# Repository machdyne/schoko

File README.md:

# Schoko Computer

Schoko is an FPGA computer designed by Lone Dynamics Corporation.

This repo contains schematics, pinouts, a 3D-printable case, example gateware and documentation.

Find more information on the [Schoko product page](https://machdyne.com/product/schoko-computer/).

## Programming Schoko

Schoko has a JTAG interface and ships with a [DFU bootloader](https://github.com/machdyne/tinydfu-bootloader) that allows the included flash [MMOD](https://machdyne.com/product/mmod) to be programmed over the USB-C port.

The first 1MB of the flash MMOD is reserved for the bootloader, the next 3MB are reserved for user gateware and the remaining space is available for user data.

### DFU

The DFU bootloader is available for 5 seconds after power-on, issuing a DFU command during this period will stop the boot process until the DFU device is detached. If no command is received the boot process will continue and the user gateware will be loaded.

Install [dfu-util](http://dfu-util.sourceforge.net) (Debian/Ubuntu):

```
$ sudo apt install dfu-util
```

Update the user gateware on the flash MMOD:

```
$ sudo dfu-util -a 0 -D image.bit
```

Detach the DFU device and continue the boot process:

```
$ sudo dfu-util -a 0 -e
```

It is possible to update the bootloader itself using DFU but you shouldn't attempt this unless you have a JTAG programmer (or another method to program the MMOD) available, in case you need to restore the bootloader.

### JTAG

These examples assume you're using a "USB Blaster" JTAG cable, see the header pinout below. You will need to have [openFPGALoader](https://github.com/trabucayre/openFPGALoader) installed.

Program the configuration SRAM:

```
openFPGALoader -c usb-blaster image.bit
```

Program the flash MMOD:

```
openFPGALoader -f -c usb-blaster images/bootloader/tinydfu_schoko.bit
```

## Blinky 

Building the blinky example requires [Yosys](https://github.com/YosysHQ/yosys), [nextpnr-ecp5](https://github.com/YosysHQ/nextpnr) and [Project Trellis](https://github.com/YosysHQ/prjtrellis).

Assuming they are installed, you can simply type `make` to build the gateware, which will be written to output/blinky.bin. You can then use [openFPGALoader](https://github.com/trabucayre/openFPGALoader) or dfu-util to write the gateware to the device.

## Linux

See the [Kakao Linux](https://github.com/machdyne/kakao) repo for the latest instructions.

### Prebuilt Images

Copy the files from the `images/linux` directory to the root directory of a FAT-formatted MicroSD card.

Schoko ships with LiteX gateware on the user gateware section of the MMOD that is compatible with these images. If you plug a USB-UART into PMODA you should be able to interact with LiteX and view the Linux boot messages. After several seconds the Linux penguin should appear on the screen (HDMI) followed by a login prompt.

You can switch to the VGA gateware with:
 
```
$ sudo dfu-util -a 0 -D images/v1_vga/schoko.bit
```

Note: It should be possible to store the Linux images on the MMOD itself and boot Linux without any MicroSD card but this is not yet supported.

### Building Linux

Please follow the setup instructions in the [linux-on-litex-vexriscv](https://github.com/litex-hub/linux-on-litex-vexriscv) repo and then:

1. Build the Linux-capable gateware:

```
$ cd linux-on-litex-vexriscv
$ ./make.py --board schoko --uart-baudrate 1000000 --build
$ ls build/schoko
```

2. Write the gateware to the MMOD using USB DFU:

```
$ sudo dfu-util -a 0 -D build/schoko/gateware/schoko.bit
```

3. Copy the device tree binary `build/schoko/schoko.dtb` to a FAT-formatted MicroSD card.

4. Build the Linux kernel and root filesystem:

```
$ cd ..
$ git clone http://github.com/buildroot/buildroot
$ cd buildroot
$ make BR2_EXTERNAL=../linux-on-litex-vexriscv/buildroot/ litex_vexriscv_usbhost_defconfig
```

Optionally customize the kernel and buildroot packages:

```
$ make menuconfig
```

Build the kernel and rootfs:

```
$ make
$ ls output/images
```

5. Copy the `Image` and `rootfs.cpio` files from output/images to the MicroSD card.

6. Copy the OpenSBI binary (included in this repo as `schoko/images/linux/opensbi.bin`) to the MicroSD card. Alternatively, you can build this binary by following [these instructions](https://github.com/litex-hub/linux-on-litex-vexriscv#-generating-the-opensbi-binary-optional).

7. Copy `schoko/images/linux/boot.json` to the MicroSD card.

8. Power-cycle Schoko and if a USB-UART PMOD is attached to PMODA you should see the LiteX memory test and then the Linux boot messages. After Linux has finished booting you should see a login prompt on the serial console and the HDMI display.

## LiteX

### Installing LiteX

If you haven't yet installed LiteX please see the [LiteX quick start guide](https://github.com/enjoy-digital/litex#quick-start-guide) for details on installing LiteX.

### Building Custom Gateware

Build the LiteX gateware:

```
$ cd litex-boards/litex_boards/targets
$ ./machdyne_schoko.py --cpu-type=vexriscv --cpu-variant=lite --sys-clk-freq 40000000 --uart-baudrate 1000000 --uart-name serial --build
```

Program the LiteX gateware to SRAM over JTAG:

```
$ ./machdyne_schoko.py --cable usb-blaster --load
```

Or program the LiteX gateware to flash over DFU:

```
$ sudo dfu-util -a 0 -D build/machdyne_schoko/gateware/machdyne_schoko.bit
```

## JTAG Header

The JTAG header can be used to program the FPGA SRAM as well as the MMOD flash memory. 

```
1 2
3 4
5 6
```

| Pin | Signal |
| --- | ------ |
| 1 | TCK |
| 2 | TDI |
| 3 | TDO |
| 4 | TMS |
| 5 | 3V3 |
| 6 | GND |

## Board Revisions

| Revision | Notes |
| -------- | ----- |
| V0 | Internal prototype |
| V1 | Initial production boards |
| V1A | Identical to V1 except for minor aesthetic changes on the silkscreen |
| V2 | Work-in-progress; adds SD-mode for MicroSD card |

## License

The contents of this repo are released under the [Lone Dynamics Open License](LICENSE.md) with the following exceptions:

- The KiCad design files contain parts of the [kicad-pmod](https://github.com/mithro/kicad-pmod) library which is released under the [Apache License, Version 2.0](https://www.apache.org/licenses/LICENSE-2.0.html).

- The KiCad design files may contain symbols and footprints released under other licenses; please contact us if we've failed to give proper attribution.

Note: You can use these designs for commercial purposes but we ask that instead of producing exact clones, that you either replace our trademarks and logos with your own or add your own next to ours.

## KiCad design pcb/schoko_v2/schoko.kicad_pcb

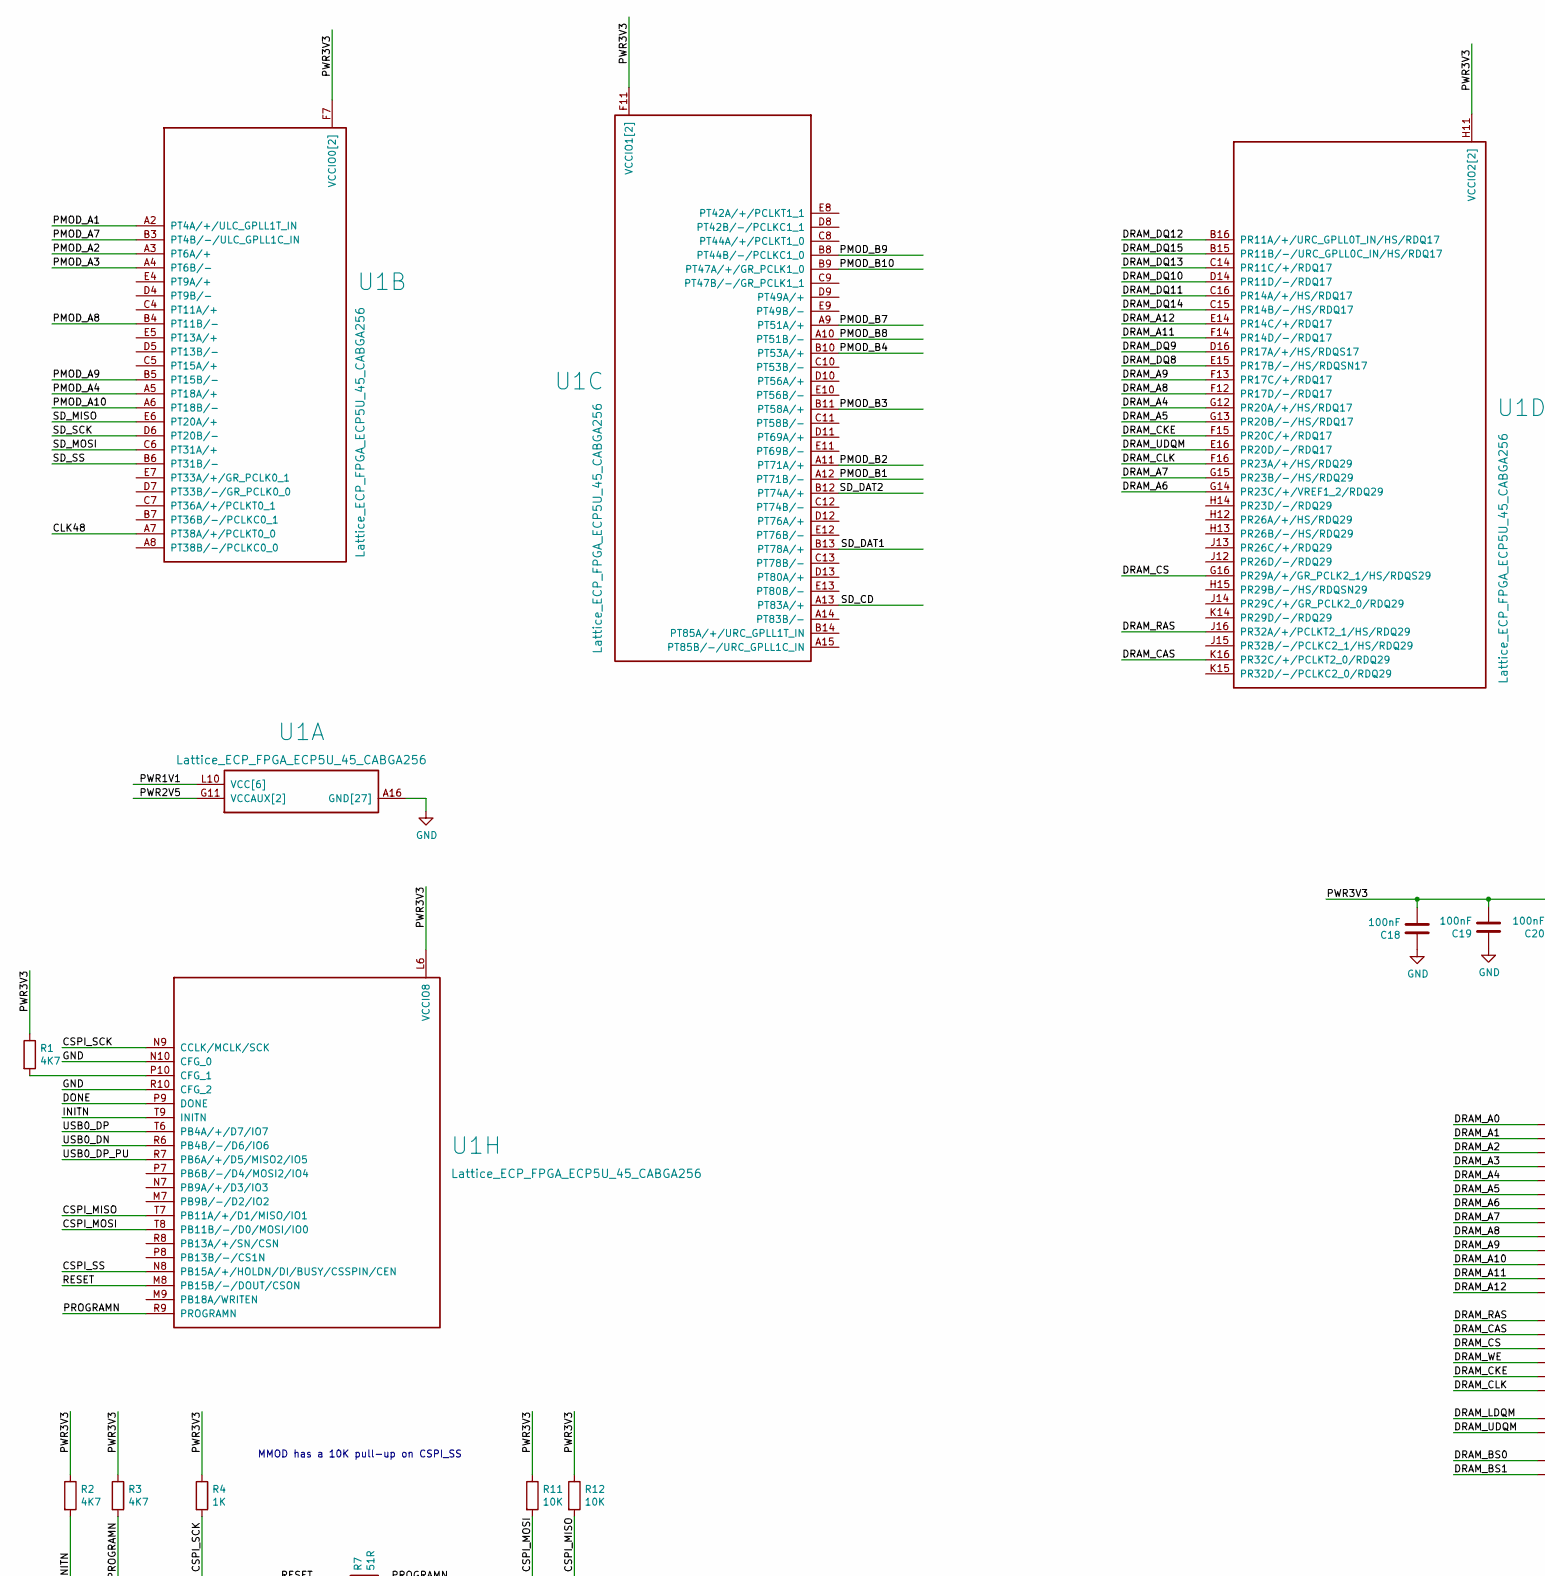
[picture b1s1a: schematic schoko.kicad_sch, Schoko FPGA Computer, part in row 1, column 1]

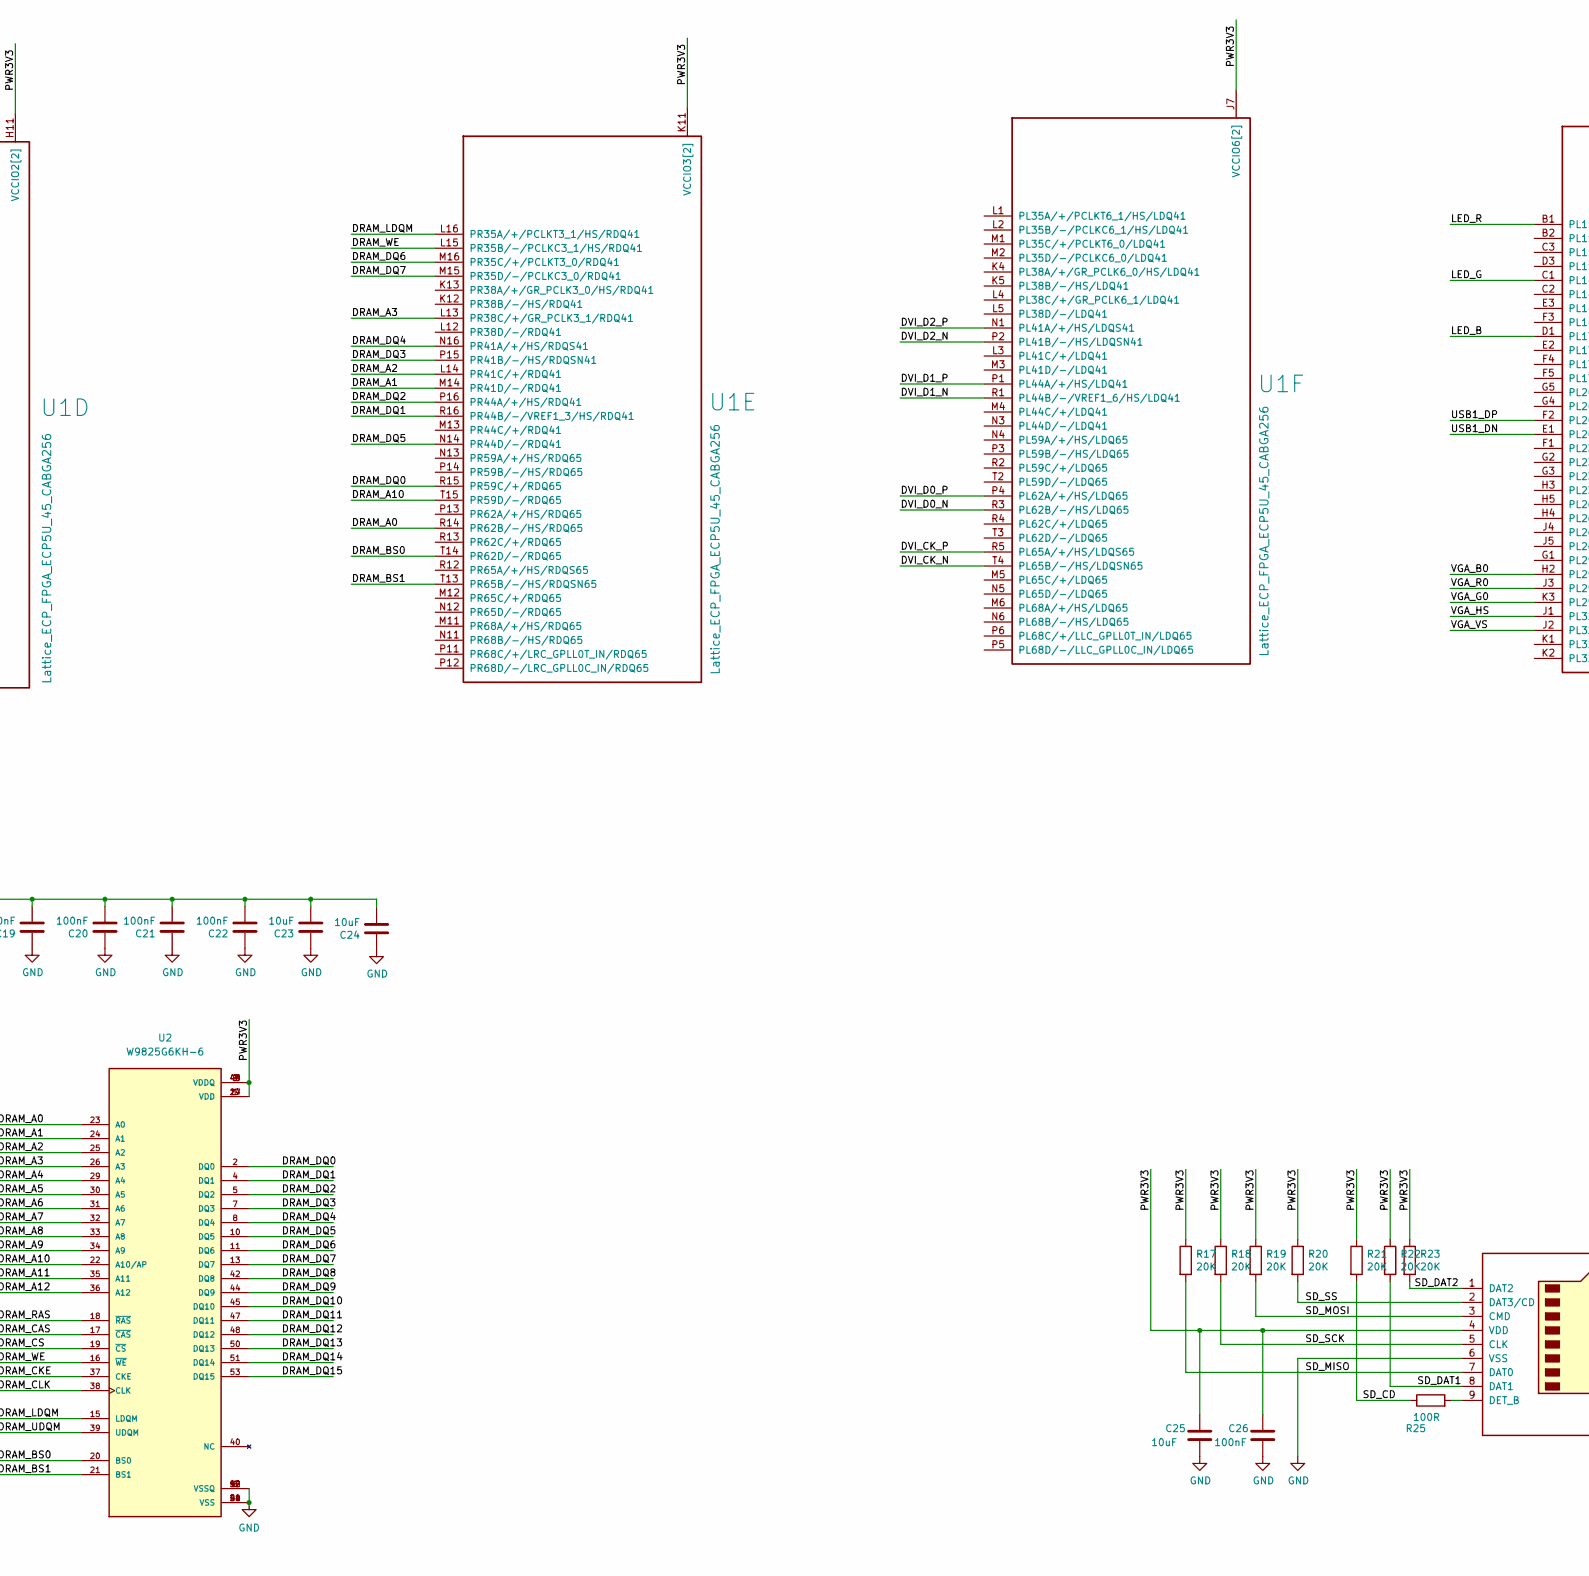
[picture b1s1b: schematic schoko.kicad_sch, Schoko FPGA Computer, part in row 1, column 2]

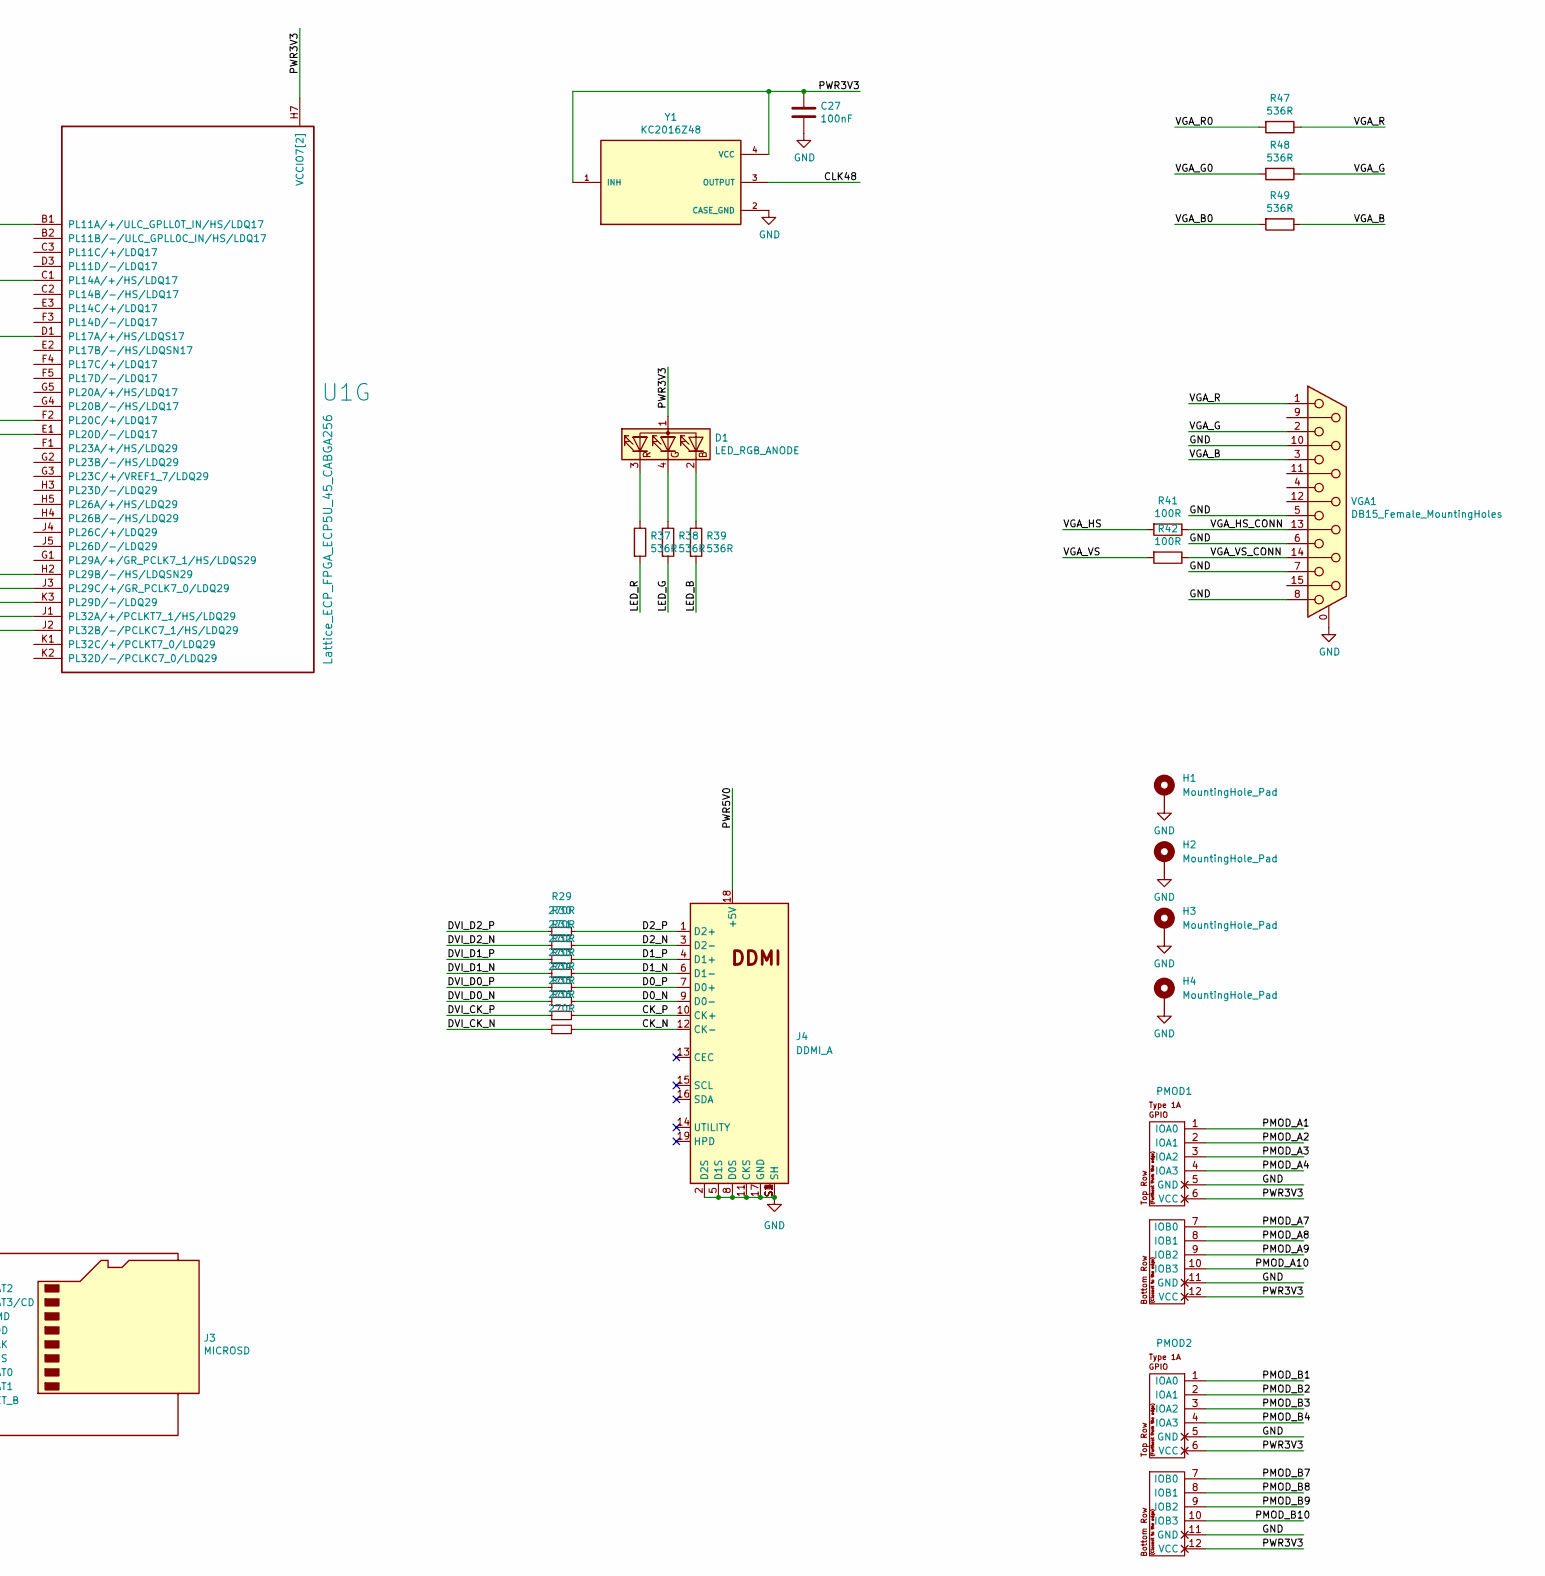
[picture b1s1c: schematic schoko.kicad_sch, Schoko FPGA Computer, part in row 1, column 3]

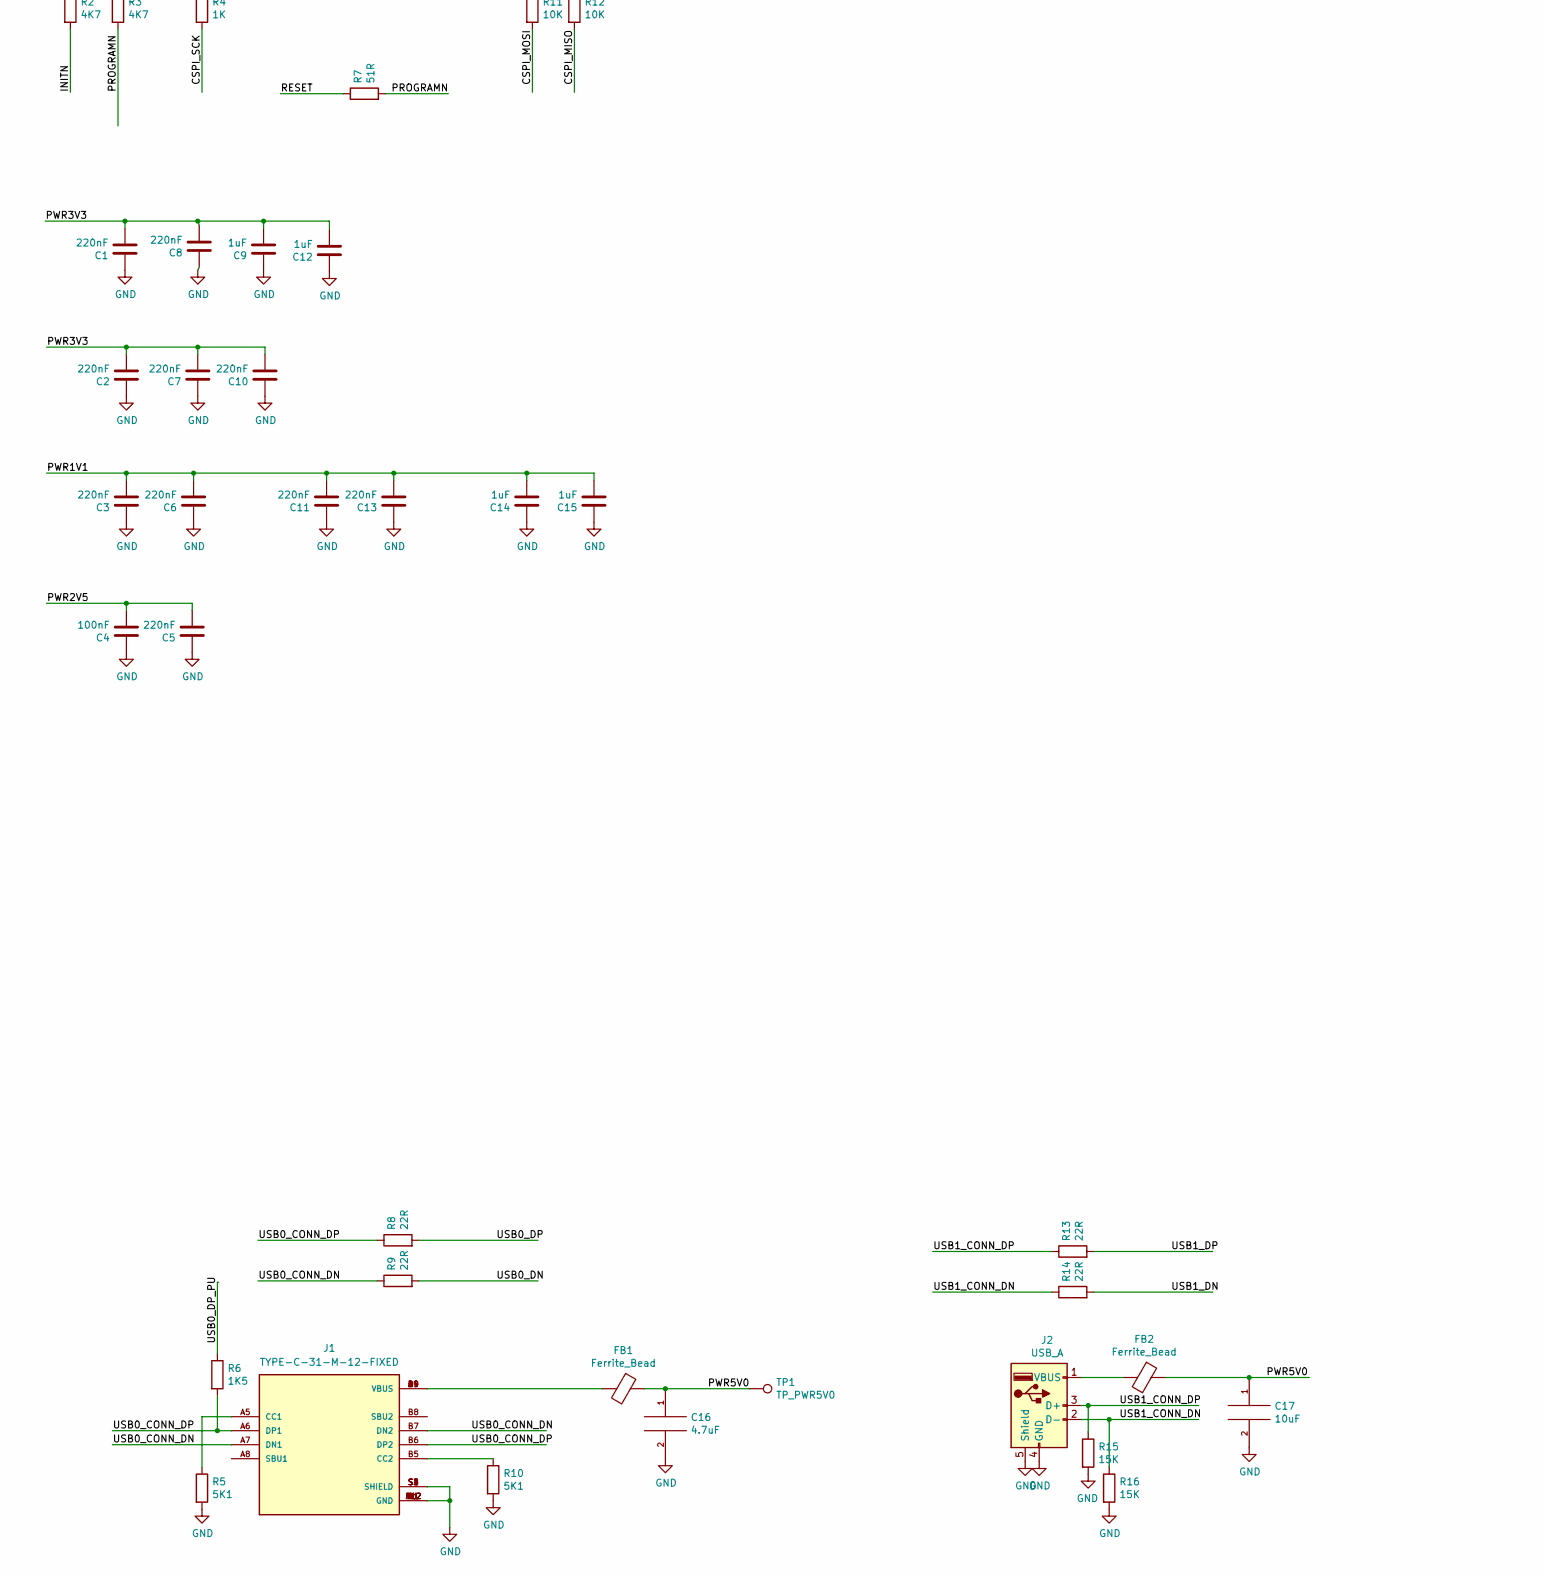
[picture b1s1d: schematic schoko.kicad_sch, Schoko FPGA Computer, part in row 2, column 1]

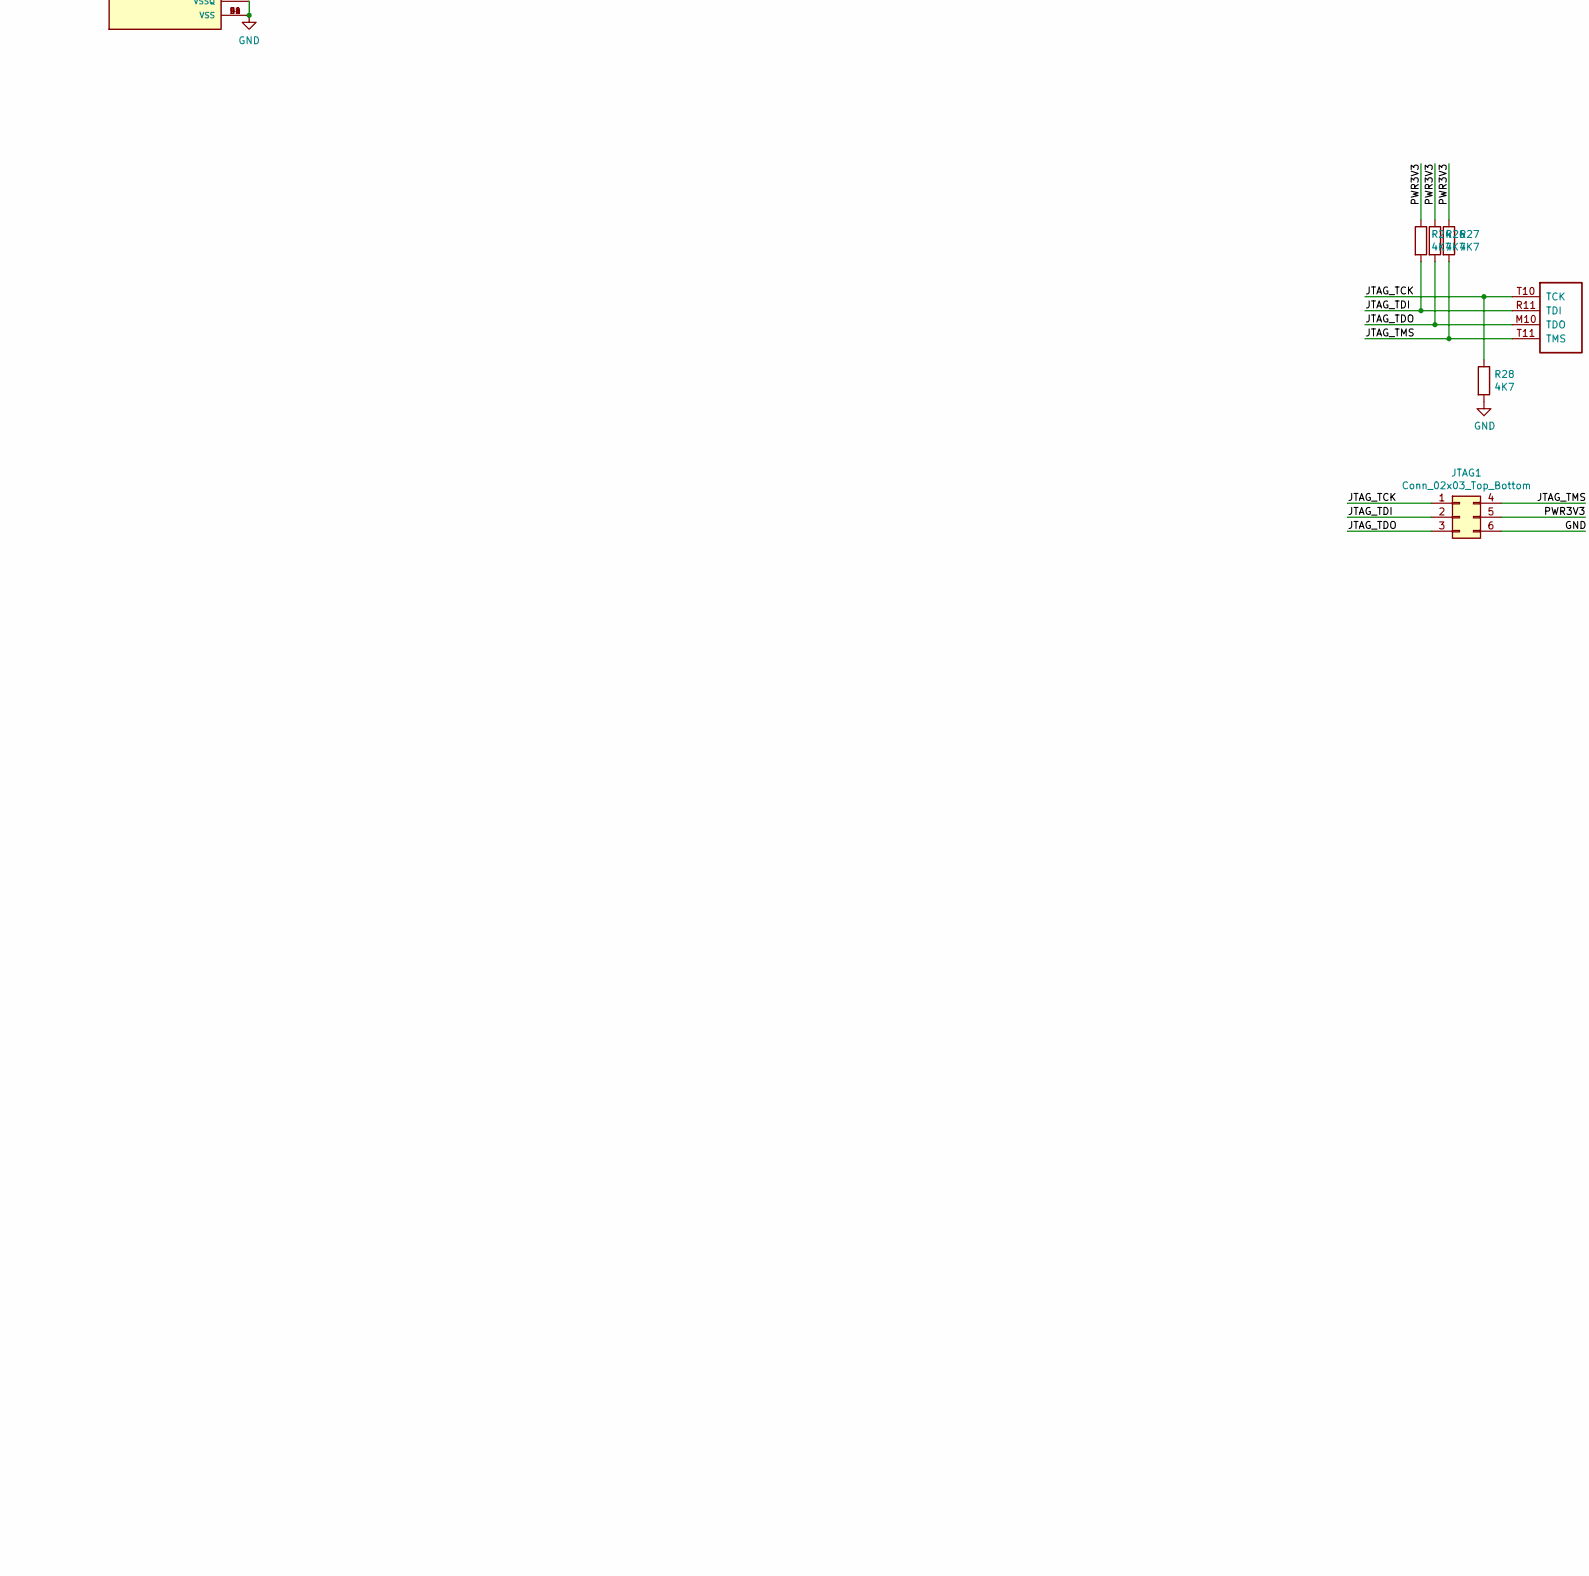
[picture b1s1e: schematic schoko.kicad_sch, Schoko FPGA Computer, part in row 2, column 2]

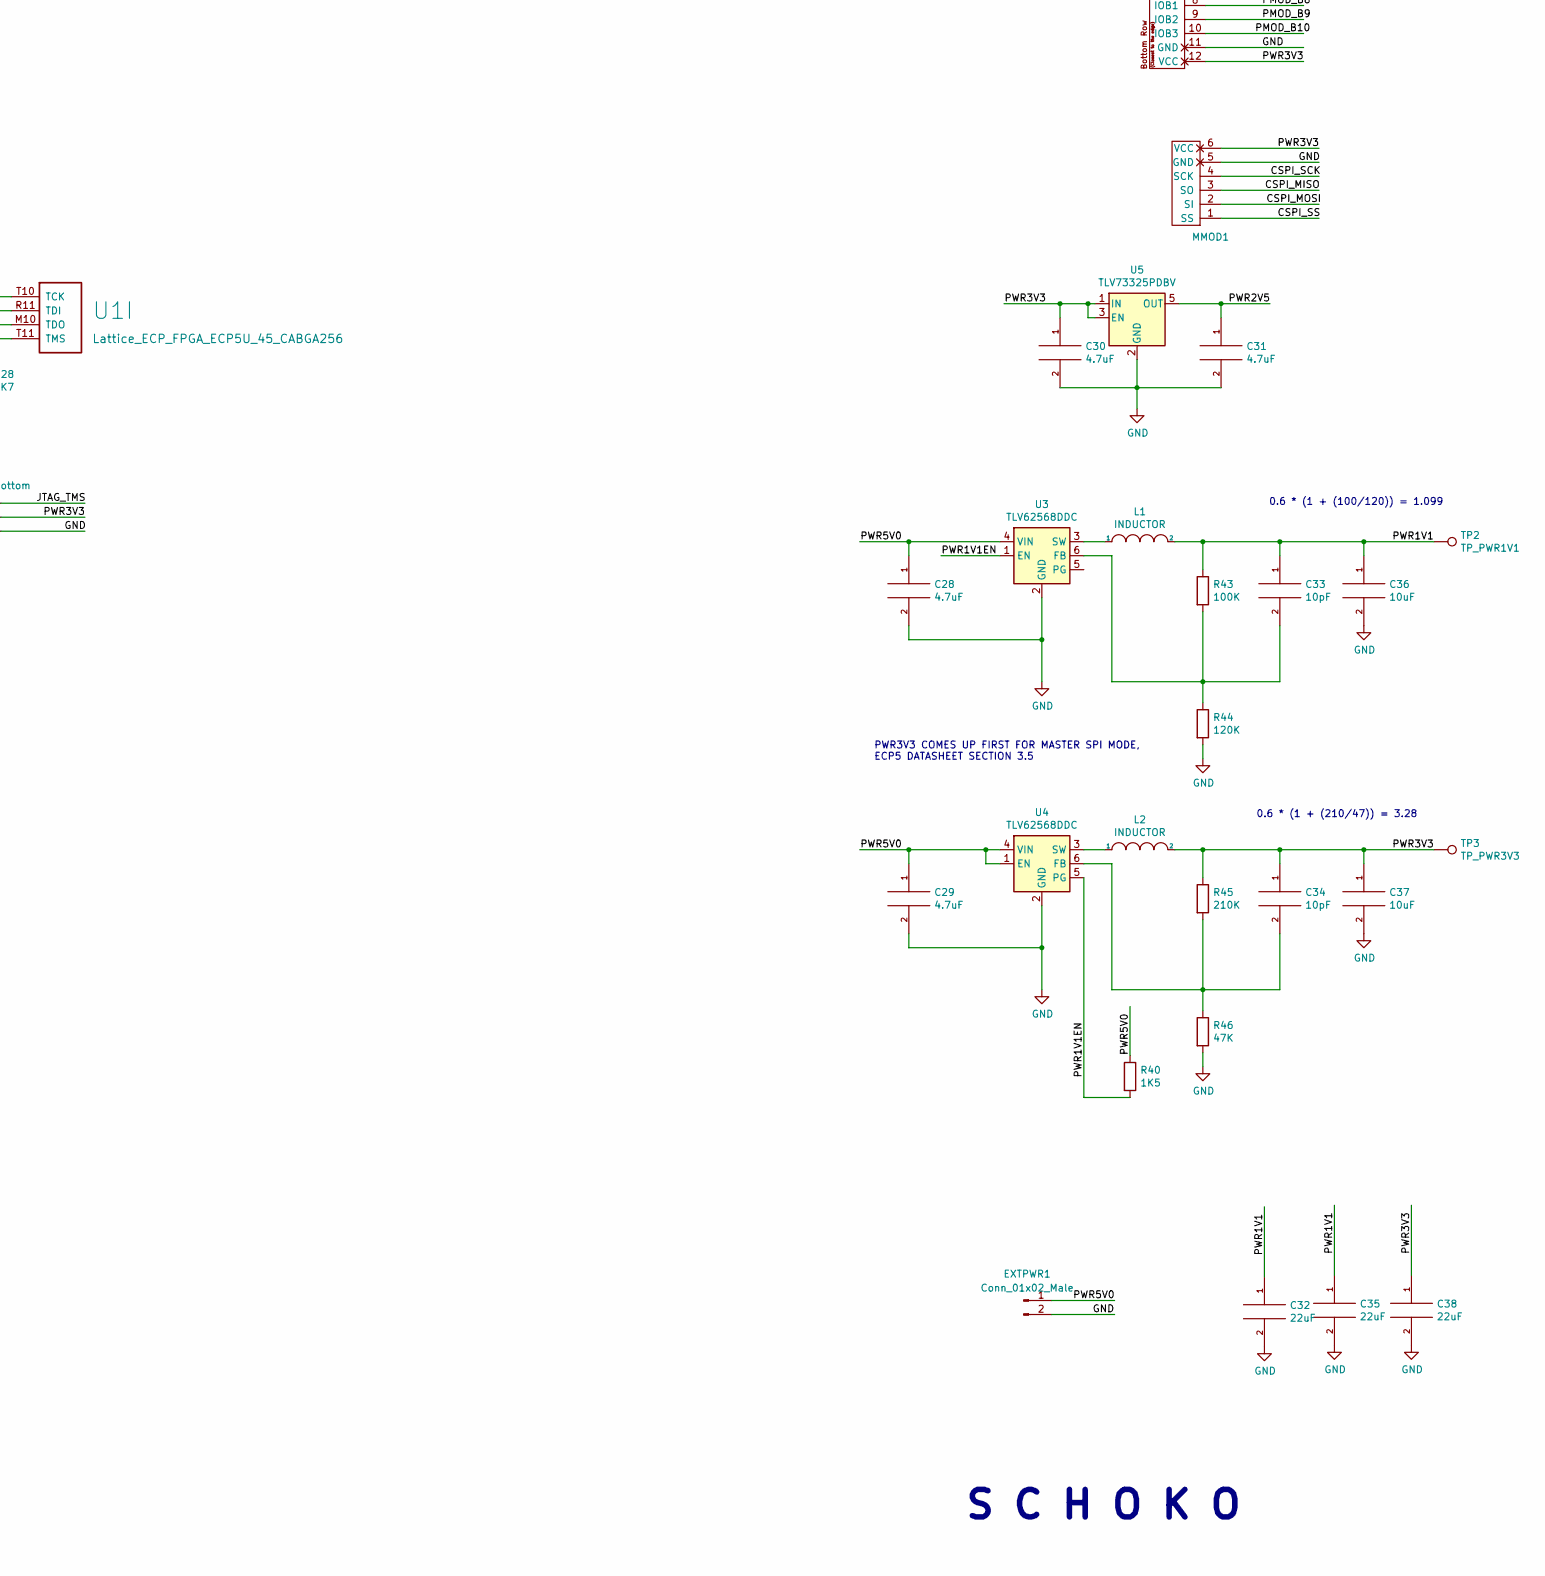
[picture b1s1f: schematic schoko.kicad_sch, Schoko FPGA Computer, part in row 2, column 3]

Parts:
C1, C2, C3, C5, C6, C7, C8, C10, C11, C13: 220nF; R_0603_1608Metric
C4, C18, C19, C20, C21, C22, C26, C27: 100nF; R_0603_1608Metric
C9, C12, C14, C15: 1uF; R_0603_1608Metric
C16: 4.7uF; R_0603_1608Metric
C17, C23, C24, C25: 10uF; R_0603_1608Metric
C28, C29, C30, C31: 4.7uF; C_0603_1608Metric
C32, C35, C38: 22uF; C_0603_1608Metric
C33, C34: 10pF; C_0603_1608Metric
C36, C37: 10uF; C_0603_1608Metric
D1: LED_RGB_ANODE; LED_RGB_0606_CHANZON
EXTPWR1: Conn_01x02_Male; PinHeader_1x02_P2.54mm_Vertical
FB1, FB2: Ferrite_Bead; R_0603_1608Metric
H1, H2, H3, H4: MountingHole_Pad; MountingHole_3.2mm_M3_Pad
J1: TYPE-C-31-M-12-FIXED; USB_C_Receptacle_HRO_TYPE-C-31-M-12-BIG-PADS; PARTREV A
J2: USB_A; USB_A_Stewart_SS-52100-001_Horizontal
J3: MICROSD; SDCARD
J4: DDMI_A; HDMI_TE_1827059-3-FIXED
JTAG1: Conn_02x03_Top_Bottom; PinHeader_2x03_P2.54mm_Vertical
L1, L2: INDUCTOR; L_0805_2012Metric
MMOD1: PMOD-Device-x1-Type-2-SPI; MMOD_Host_Socket
PMOD1, PMOD2: PMOD-Device-x2-Type-1A-GPIO; PMOD_2x06_HOST
R1, R2, R3, R24, R26, R27, R28: 4K7; R_0603_1608Metric
R4: 1K; R_0603_1608Metric
R5, R10: 5K1; R_0603_1608Metric
R6, R40: 1K5; R_0603_1608Metric
R7: 51R; R_0603_1608Metric
R8, R9, R13, R14: 22R; R_0603_1608Metric
R11, R12: 10K; R_0603_1608Metric
R15, R16: 15K; R_0603_1608Metric
R17, R18, R19, R20, R21, R22, R23: 20K; R_0603_1608Metric
R25, R41, R42: 100R; R_0603_1608Metric
R29, R30, R31, R32, R33, R34, R35, R36: 270R; R_0603_1608Metric
R37, R38, R39, R47, R48, R49: 536R; R_0603_1608Metric
R43: 100K; R_0603_1608Metric
R44: 120K; R_0603_1608Metric
R45: 210K; R_0603_1608Metric
R46: 47K; R_0603_1608Metric
TP1: TP_PWR5V0; TestPoint_THTPad_D1.0mm_Drill0.5mm
TP2: TP_PWR1V1; TestPoint_THTPad_D1.0mm_Drill0.5mm
TP3: TP_PWR3V3; TestPoint_THTPad_D1.0mm_Drill0.5mm
U1: Lattice_ECP_FPGA_ECP5U_45_CABGA256; BGA-256_14.0x14.0mm_Layout16x16_P0.8mm_Ball0.45mm_Pad0.32mm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
U2: W9825G6KH-6; SOP80P1176X120-54N; PARTREV A05
U3, U4: TLV62568DDC; SOT-23-6
U5: TLV73325PDBV; SOT-23-5
VGA1: DB15_Female_MountingHoles; DSUB-15-HD_Female_Horizontal_P2.29x1.98mm_EdgePinOffset3.03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
Y1: KC2016Z48; OSC_KC2016Z13.5600C1KX00; PARTREV November 2020

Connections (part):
/CK_N: J4.12 (CK-), R36.2
/CK_P: J4.10 (CK+), R35.2
/CLK48: U1.A7 (PT38A/+/PCLKT0_0), Y1.3 (OUTPUT)
/CSPI_MISO: MMOD1.3 (SO), R12.2, U1.T7 (PB11A/+/D1/MISO/IO1)
/CSPI_MOSI: MMOD1.2 (SI), R11.2, U1.T8 (PB11B/-/D0/MOSI/IO0)
/CSPI_SCK: MMOD1.4 (SCK), R4.2, U1.N9 (CCLK/MCLK/SCK)
/CSPI_SS: MMOD1.1 (SS), U1.N8 (PB15A/+/HOLDN/DI/BUSY/CSSPIN/CEN)
/D0_N: J4.9 (D0-), R34.2
/D0_P: J4.7 (D0+), R33.2
/D1_N: J4.6 (D1-), R32.2
/D1_P: J4.4 (D1+), R31.2
/D2_N: J4.3 (D2-), R30.2
/D2_P: J4.1 (D2+), R29.2
/DONE: U1.P9 (DONE)
/DRAM_A0: U1.R14 (PR62B/-/HS/RDQ65), U2.23 (A0)
/DRAM_A1: U1.M14 (PR41D/-/RDQ41), U2.24 (A1)
/DRAM_A2: U1.L14 (PR41C/+/RDQ41), U2.25 (A2)
/DRAM_A3: U1.L13 (PR38C/+/GR_PCLK3_1/RDQ41), U2.26 (A3)
/DRAM_A4: U1.G12 (PR20A/+/HS/RDQ17), U2.29 (A4)
/DRAM_A5: U1.G13 (PR20B/-/HS/RDQ17), U2.30 (A5)
/DRAM_A6: U1.G14 (PR23C/+/VREF1_2/RDQ29), U2.31 (A6)
/DRAM_A7: U1.G15 (PR23B/-/HS/RDQ29), U2.32 (A7)
/DRAM_A8: U1.F12 (PR17D/-/RDQ17), U2.33 (A8)
/DRAM_A9: U1.F13 (PR17C/+/RDQ17), U2.34 (A9)
/DRAM_A10: U1.T15 (PR59D/-/RDQ65), U2.22 (A10/AP)
/DRAM_A11: U1.F14 (PR14D/-/RDQ17), U2.35 (A11)
/DRAM_A12: U1.E14 (PR14C/+/RDQ17), U2.36 (A12)
/DRAM_BS0: U1.T14 (PR62D/-/RDQ65), U2.20 (BS0)
/DRAM_BS1: U1.T13 (PR65B/-/HS/RDQSN65), U2.21 (BS1)
/DRAM_CAS: U1.K16 (PR32C/+/PCLKT2_0/RDQ29), U2.17 (~CAS)
/DRAM_CKE: U1.F15 (PR20C/+/RDQ17), U2.37 (CKE)
/DRAM_CLK: U1.F16 (PR23A/+/HS/RDQ29), U2.38 (CLK)
/DRAM_CS: U1.G16 (PR29A/+/GR_PCLK2_1/HS/RDQS29), U2.19 (~CS)
/DRAM_DQ0: U1.R15 (PR59C/+/RDQ65), U2.2 (DQ0)
/DRAM_DQ1: U1.R16 (PR44B/-/VREF1_3/HS/RDQ41), U2.4 (DQ1)
/DRAM_DQ2: U1.P16 (PR44A/+/HS/RDQ41), U2.5 (DQ2)
/DRAM_DQ3: U1.P15 (PR41B/-/HS/RDQSN41), U2.7 (DQ3)
/DRAM_DQ4: U1.N16 (PR41A/+/HS/RDQS41), U2.8 (DQ4)
/DRAM_DQ5: U1.N14 (PR44D/-/RDQ41), U2.10 (DQ5)
/DRAM_DQ6: U1.M16 (PR35C/+/PCLKT3_0/RDQ41), U2.11 (DQ6)
/DRAM_DQ7: U1.M15 (PR35D/-/PCLKC3_0/RDQ41), U2.13 (DQ7)
/DRAM_DQ8: U1.E15 (PR17B/-/HS/RDQSN17), U2.42 (DQ8)
/DRAM_DQ9: U1.D16 (PR17A/+/HS/RDQS17), U2.44 (DQ9)
/DRAM_DQ10: U1.D14 (PR11D/-/RDQ17), U2.45 (DQ10)
/DRAM_DQ11: U1.C16 (PR14A/+/HS/RDQ17), U2.47 (DQ11)
/DRAM_DQ12: U1.B16 (PR11A/+/URC_GPLL0T_IN/HS/RDQ17), U2.48 (DQ12)
/DRAM_DQ13: U1.C14 (PR11C/+/RDQ17), U2.50 (DQ13)
/DRAM_DQ14: U1.C15 (PR14B/-/HS/RDQ17), U2.51 (DQ14)
/DRAM_DQ15: U1.B15 (PR11B/-/URC_GPLL0C_IN/HS/RDQ17), U2.53 (DQ15)
/DRAM_LDQM: U1.L16 (PR35A/+/PCLKT3_1/HS/RDQ41), U2.15 (LDQM)
/DRAM_RAS: U1.J16 (PR32A/+/PCLKT2_1/HS/RDQ29), U2.18 (~RAS)
/DRAM_UDQM: U1.E16 (PR20D/-/RDQ17), U2.39 (UDQM)
/DRAM_WE: U1.L15 (PR35B/-/PCLKC3_1/HS/RDQ41), U2.16 (~WE)
/DVI_CK_N: R36.1, U1.T4 (PL65B/-/HS/LDQSN65)
/DVI_CK_P: R35.1, U1.R5 (PL65A/+/HS/LDQS65)
/DVI_D0_N: R34.1, U1.R3 (PL62B/-/HS/LDQ65)
/DVI_D0_P: R33.1, U1.P4 (PL62A/+/HS/LDQ65)
/DVI_D1_N: R32.1, U1.R1 (PL44B/-/VREF1_6/HS/LDQ41)
/DVI_D1_P: R31.1, U1.P1 (PL44A/+/HS/LDQ41)
/DVI_D2_N: R30.1, U1.P2 (PL41B/-/HS/LDQSN41)
/DVI_D2_P: R29.1, U1.N1 (PL41A/+/HS/LDQS41)
/INITN: R2.2, U1.T9 (INITN)
/JTAG_TCK: JTAG1.1, R28.1, U1.T10 (TCK)
/JTAG_TDI: JTAG1.2, R24.2, U1.R11 (TDI)
/JTAG_TDO: JTAG1.3, R26.2, U1.M10 (TDO)
/JTAG_TMS: JTAG1.4, R27.2, U1.T11 (TMS)
/LED_B: R39.2, U1.D1 (PL17A/+/HS/LDQS17)
/LED_G: R38.2, U1.C1 (PL14A/+/HS/LDQ17)
/LED_R: R37.2, U1.B1 (PL11A/+/ULC_GPLL0T_IN/HS/LDQ17)
/PMOD_A1: PMOD1.1 (IOA0), U1.A2 (PT4A/+/ULC_GPLL1T_IN)
/PMOD_A2: PMOD1.2 (IOA1), U1.A3 (PT6A/+)
/PMOD_A3: PMOD1.3 (IOA2), U1.A4 (PT6B/-)
/PMOD_A4: PMOD1.4 (IOA3), U1.A5 (PT18A/+)
/PMOD_A7: PMOD1.7 (IOB0), U1.B3 (PT4B/-/ULC_GPLL1C_IN)
/PMOD_A8: PMOD1.8 (IOB1), U1.B4 (PT11B/-)
/PMOD_A9: PMOD1.9 (IOB2), U1.B5 (PT15B/-)
/PMOD_A10: PMOD1.10 (IOB3), U1.A6 (PT18B/-)
/PMOD_B1: PMOD2.1 (IOA0), U1.A12 (PT71B/-)
/PMOD_B2: PMOD2.2 (IOA1), U1.A11 (PT71A/+)
/PMOD_B3: PMOD2.3 (IOA2), U1.B11 (PT58A/+)
/PMOD_B4: PMOD2.4 (IOA3), U1.B10 (PT53A/+)
/PMOD_B7: PMOD2.7 (IOB0), U1.A9 (PT51A/+)
/PMOD_B8: PMOD2.8 (IOB1), U1.A10 (PT51B/-)
/PMOD_B9: PMOD2.9 (IOB2), U1.B8 (PT44B/-/PCLKC1_0)
/PMOD_B10: PMOD2.10 (IOB3), U1.B9 (PT47A/+/GR_PCLK1_0)
/PROGRAMN: R3.2, R7.2, U1.R9 (PROGRAMN)
/PWR1V1: C3.2, C6.2, C11.2, C13.2, C14.2, C15.2, C32.1, C33.1, C35.1, C36.1, L1.2, R43.1, TP2.1, U1.G6 (VCC[6]), U1.G7 (VCC[6]), U1.G9 (VCC[6]), U1.L8 (VCC[6]), U1.L9 (VCC[6]), U1.L10 (VCC[6])
/PWR1V1EN: R40.2, U3.1 (EN), U4.5 (PG)
/PWR2V5: C4.2, C5.2, C31.1, U1.G11 (VCCAUX[2]), U1.L7 (VCCAUX[2]), U5.5 (OUT)
/PWR3V3: C1.2, C2.2, C7.2, C8.2, C9.2, C10.2, C12.2, C18.2, C19.2, C20.2, C21.2, C22.2, C23.2, C24.2, C25.1, C26.1, C27.1, C30.1, C34.1, C37.1, C38.1, D1.1 (A), J3.4 (VDD), JTAG1.5, L2.2, MMOD1.6 (VCC), PMOD1.6 (VCC), PMOD1.12 (VCC), PMOD2.6 (VCC), PMOD2.12 (VCC), R1.1, R2.1, R3.1, R4.1, R11.1, R12.1, R17.1, R18.1, R19.1, R20.1, R21.1, R22.1, R23.1, R24.1, R26.1, R27.1, R45.1, TP3.1, U1.F6 (VCCIO0[2]), U1.F7 (VCCIO0[2]), U1.F10 (VCCIO1[2]), U1.F11 (VCCIO1[2]), U1.H6 (VCCIO7[2]), U1.H7 (VCCIO7[2]), U1.H11 (VCCIO2[2]), U1.J6 (VCCIO6[2]), U1.J7 (VCCIO6[2]), U1.J11 (VCCIO2[2]), U1.K11 (VCCIO3[2]), U1.L6 (VCCIO8), U1.L11 (VCCIO3[2]), U2.1 (VDD), U2.3 (VDDQ), U2.9 (VDDQ), U2.14 (VDD), U2.27 (VDD), U2.43 (VDDQ), U2.49 (VDDQ), U5.1 (IN), U5.3 (EN), Y1.1 (INH), Y1.4 (VCC)
/PWR5V0: C16.1, C17.1, C28.1, C29.1, EXTPWR1.1, FB1.1, FB2.1, J4.18 (+5V), R40.1, TP1.1, U3.4 (VIN), U4.1 (EN), U4.4 (VIN)
/RESET: R7.1, U1.M8 (PB15B/-/DOUT/CSON)
/SD_CD: R21.2, R25.1, U1.A13 (PT83A/+)
/SD_DAT1: J3.8 (DAT1), R22.2, U1.B13 (PT78A/+)
/SD_DAT2: J3.1 (DAT2), R23.2, U1.B12 (PT74A/+)
/SD_MISO: J3.7 (DAT0), R17.2, U1.E6 (PT20A/+)
/SD_MOSI: J3.3 (CMD), R19.2, U1.C6 (PT31A/+)
/SD_SCK: J3.5 (CLK), R18.2, U1.D6 (PT20B/-)
/SD_SS: J3.2 (DAT3/CD), R20.2, U1.B6 (PT31B/-)
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
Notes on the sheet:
S C H O K O
PWR3V3 COMES UP FIRST FOR MASTER SPI MODE, ECP5 DATASHEET SECTION 3.5
0.6 * (1 + (210/47)) = 3.28
MMOD has a 10K pull-up on CSPI_SS
0.6 * (1 + (100/120)) = 1.099

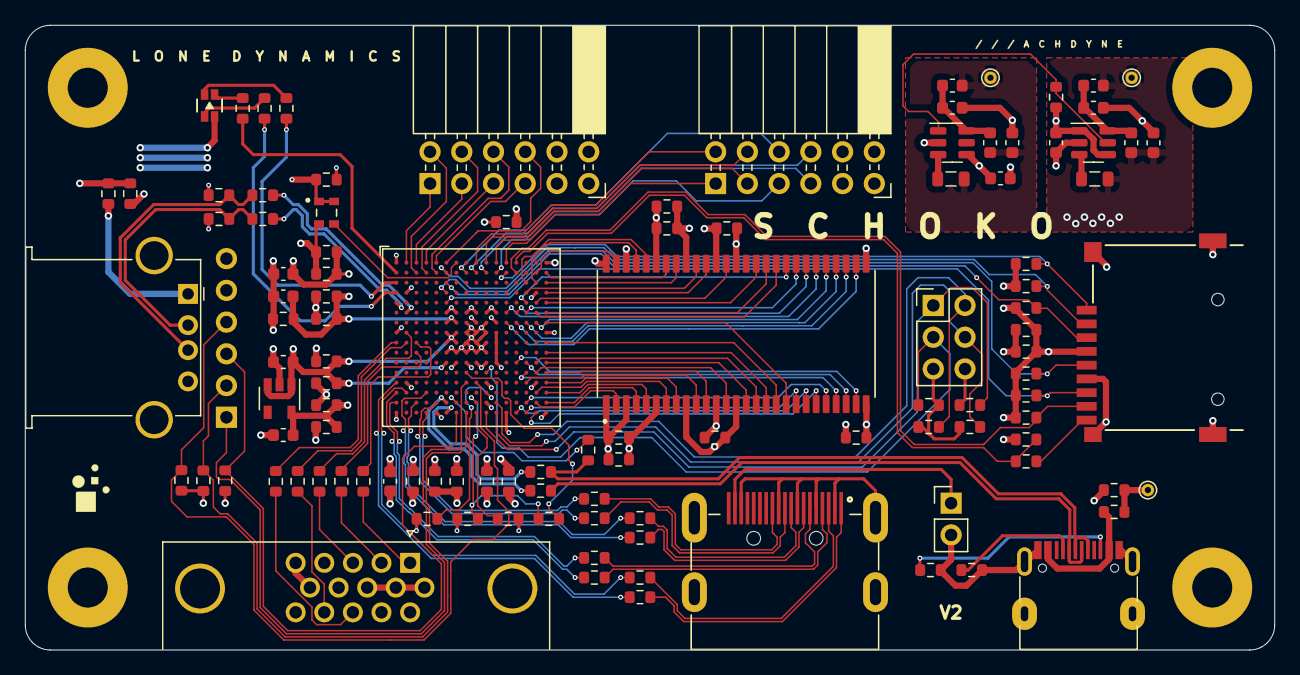
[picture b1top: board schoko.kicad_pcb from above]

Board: 4 copper layers, 100.0 x 50.0 mm, 115 parts (1 on the bottom side), 131 nets.

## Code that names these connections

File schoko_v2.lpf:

BLOCK RESETPATHS;
BLOCK ASYNCPATHS;

LOCATE COMP "CLK_48" SITE "A7";
IOBUF  PORT "CLK_48" PULLMODE=NONE IO_TYPE=LVCMOS33;
FREQUENCY PORT "CLK_48" 48 MHZ;

SYSCONFIG CONFIG_IOVOLTAGE=3.3 COMPRESS_CONFIG=ON MCCLK_FREQ=2.4 MASTER_SPI_PORT=ENABLE SLAVE_SPI_PORT=DISABLE SLAVE_PARALLEL_PORT=DISABLE CONFIG_MODE=SPI_SERIAL;

LOCATE COMP "LED_R" SITE "B1";
IOBUF  PORT "LED_R" PULLMODE=NONE IO_TYPE=LVCMOS33 DRIVE=4;

LOCATE COMP "LED_G" SITE "C1";
IOBUF  PORT "LED_G" PULLMODE=NONE IO_TYPE=LVCMOS33 DRIVE=4;

LOCATE COMP "LED_B" SITE "D1";
IOBUF  PORT "LED_B" PULLMODE=NONE IO_TYPE=LVCMOS33 DRIVE=4;

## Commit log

2022-06-23 add schematics
2022-06-25 fix labels
2022-06-27 add v2
2022-07-14 add case; update readme
2022-07-19 update readme; schoko is now in the official litex-boards repo
2022-07-21 update readme; add more details for building linux
2022-07-22 add vga images
2022-07-22 add bootloader bitstream
2022-07-22 rename common to linux
2022-07-22 update image to v1a
2022-07-26 improve fit
2022-07-30 add more complete v1 lpf
2022-07-30 update lpf
2022-10-12 remove v2
2022-11-22 update hdmi bitstream
2022-12-01 update linux, add FPU, double L2 cache
2023-02-28 fix lpf
2023-06-07 add pcb

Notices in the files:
pcb/schoko_v2/schoko.kicad_sch:
Copyright © 2022 Lone Dynamics Corporation
